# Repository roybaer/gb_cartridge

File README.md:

# GB Cartridge

This repository contains various PCB designs for Game Boy cartridges.

## Board characteristics

The individual designs have the following characteristics:

Board marking     | ROM    | RAM     | RAM backup                 | Technology | Memory Bank Controller
------------------|--------|---------|----------------------------|------------|--------------------------------
ROM+RAM(+BATT)    | 32 KiB | 8 KiB   | external battery/capacitor | SMD        | none
ROM+RAM+BATT      | 32 KiB | 8 KiB   | coin cell battery holder   | SMD        | none
ROM+RAM+BATT EVAL | 32 KiB | 8 KiB   | external battery           | THT        | none
ROM+MBC+RAM+BATT  | 1 MiB  | 128 KiB | coin cell battery holder   | SMD        | 74xx ICs loosely imitating MBC5

So far, only __ROM+RAM+BATT__ and __ROM+RAM+BATT EVAL__ have been manufactured and only the ROM related functionality has been tested.

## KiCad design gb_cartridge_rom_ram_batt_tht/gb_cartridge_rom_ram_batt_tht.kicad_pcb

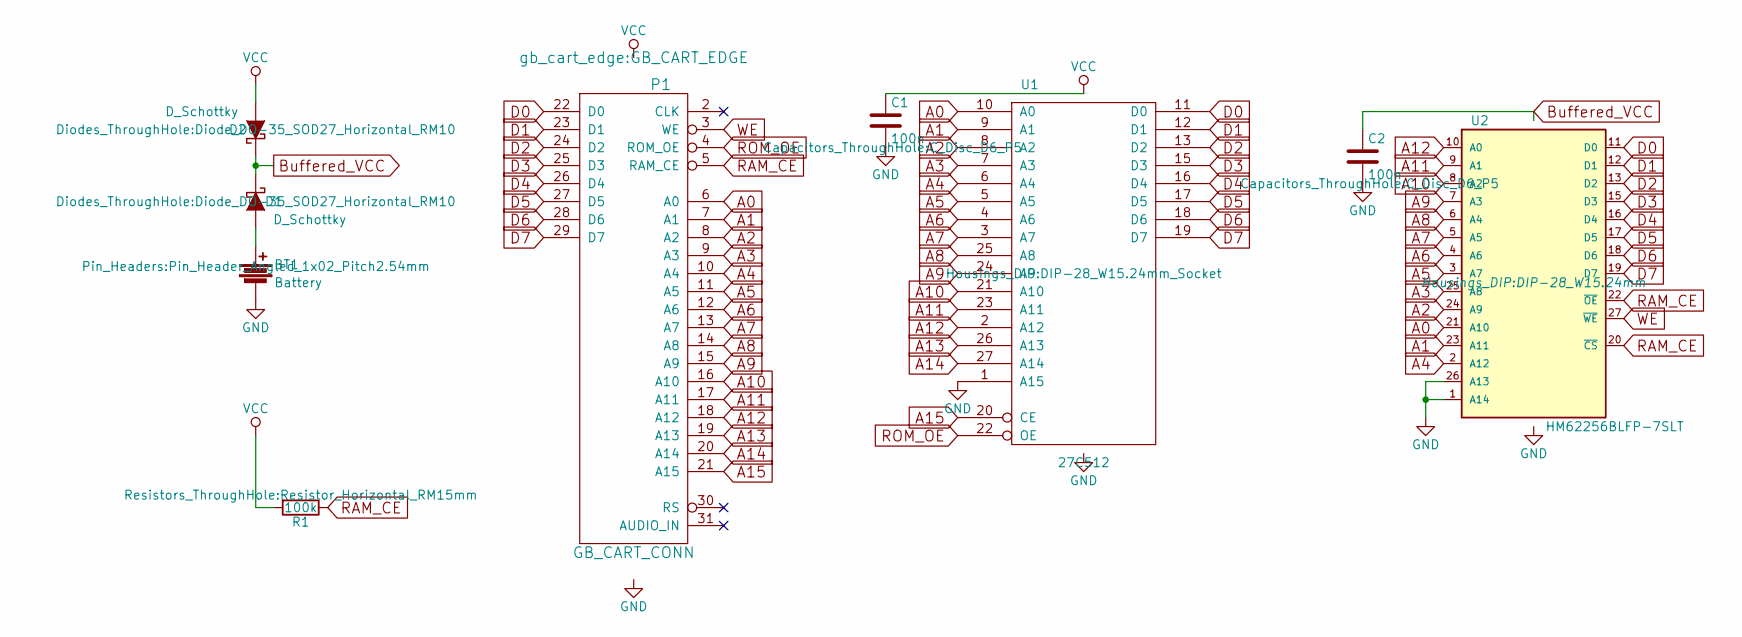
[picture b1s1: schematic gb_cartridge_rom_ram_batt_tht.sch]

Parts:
BT1: Battery; Pin_Header_Angled_1x02_Pitch2.54mm
C1, C2: 100n; C_Disc_D6_P5
D1, D2: D_Schottky; Diode_DO-35_SOD27_Horizontal_RM10
P1: GB_CART_CONN; GB_CART_EDGE
R1: 100k; Resistor_Horizontal_RM15mm
U1: 27C512; DIP-28_W15.24mm_Socket
U2: HM62256BLFP-7SLT; DIP-28_W15.24mm

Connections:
A0: P1.6 (A0), U1.10 (A0), U2.21 (A10)
A1: P1.7 (A1), U1.9 (A1), U2.23 (A11)
A2: P1.8 (A2), U1.8 (A2), U2.24 (A9)
A3: P1.9 (A3), U1.7 (A3), U2.25 (A8)
A4: P1.10 (A4), U1.6 (A4), U2.2 (A12)
A5: P1.11 (A5), U1.5 (A5), U2.3 (A7)
A6: P1.12 (A6), U1.4 (A6), U2.4 (A6)
A7: P1.13 (A7), U1.3 (A7), U2.5 (A5)
A8: P1.14 (A8), U1.25 (A8), U2.6 (A4)
A9: P1.15 (A9), U1.24 (A9), U2.7 (A3)
A10: P1.16 (A10), U1.21 (A10), U2.8 (A2)
A11: P1.17 (A11), U1.23 (A11), U2.9 (A1)
A12: P1.18 (A12), U1.2 (A12), U2.10 (A0)
A13: P1.19 (A13), U1.26 (A13)
A14: P1.20 (A14), U1.27 (A14)
A15: P1.21 (A15), U1.20 (CE)
D0: P1.22 (D0), U1.11 (D0), U2.11 (D0)
D1: P1.23 (D1), U1.12 (D1), U2.12 (D1)
D2: P1.24 (D2), U1.13 (D2), U2.13 (D2)
D3: P1.25 (D3), U1.15 (D3), U2.15 (D3)
D4: P1.26 (D4), U1.16 (D4), U2.16 (D4)
D5: P1.27 (D5), U1.17 (D5), U2.17 (D5)
D6: P1.28 (D6), U1.18 (D6), U2.18 (D6)
D7: P1.29 (D7), U1.19 (D7), U2.19 (D7)
GND: BT1.2, C1.2, C2.2, P1.32 (GND), U1.1 (A15), U1.14 (GND), U2.1 (A14), U2.14 (GND), U2.26 (A13)
unnamed: BT1.1, D1.2 (A)
RAM_CE: P1.5 (RAM_CE), R1.1, U2.20 (~CS), U2.22 (~OE)
ROM_OE: P1.4 (ROM_OE), U1.22 (OE)
WE: P1.3 (WE), U2.27 (~WE)

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
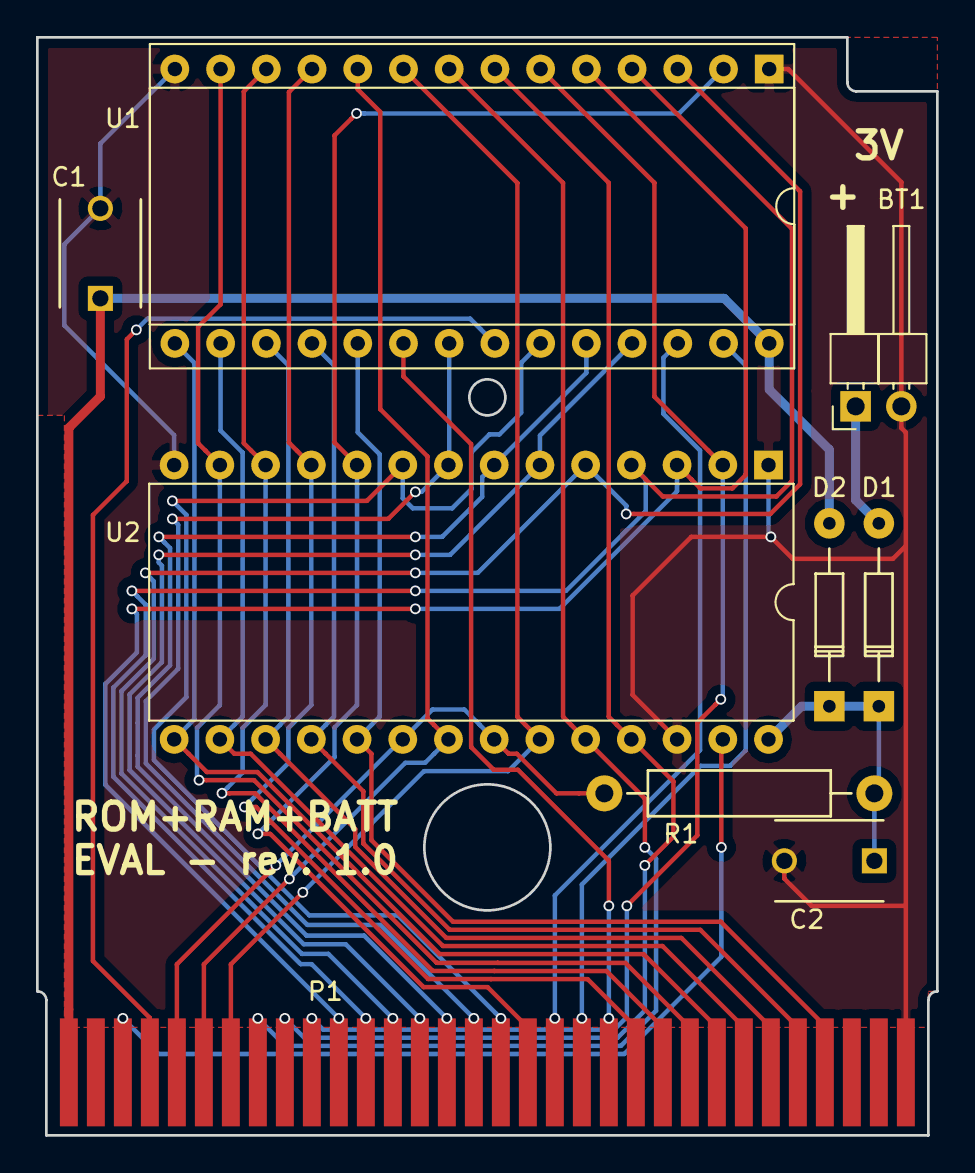
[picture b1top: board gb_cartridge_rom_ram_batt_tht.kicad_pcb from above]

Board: 2 copper layers, 50.0 x 61.0 mm, 9 parts (0 on the bottom side), 30 nets.

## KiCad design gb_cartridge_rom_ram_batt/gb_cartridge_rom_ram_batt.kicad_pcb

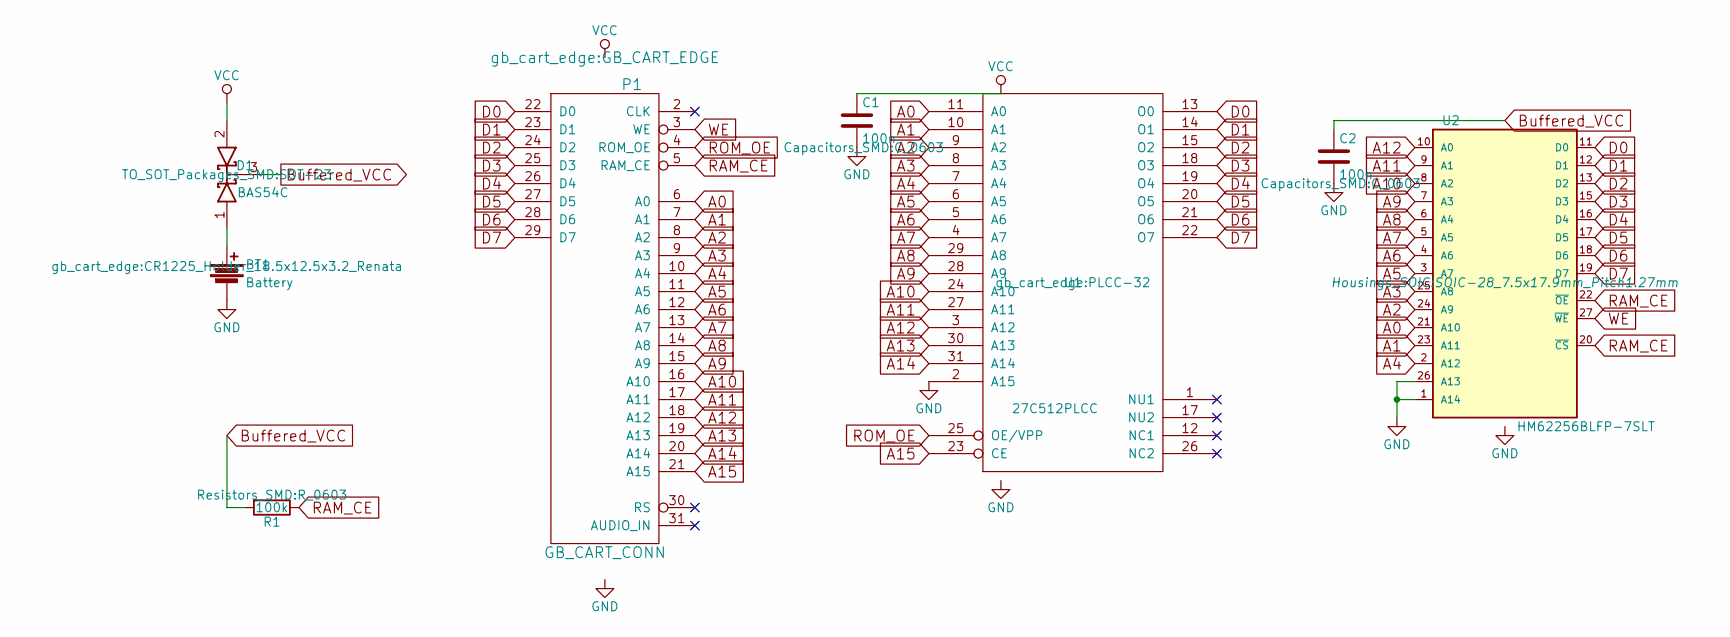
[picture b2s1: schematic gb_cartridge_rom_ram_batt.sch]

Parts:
BT1: Battery; CR1225_Holder_18.5x12.5x3.2_Renata
C1, C2: 100n; C_0603
D1: BAS54C; SOT-23
P1: GB_CART_CONN; GB_CART_EDGE
R1: 100k; R_0603
U1: 27C512PLCC; PLCC-32
U2: HM62256BLFP-7SLT; SOIC-28_7.5x17.9mm_Pitch1.27mm

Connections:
A0: P1.6 (A0), U1.11 (A0), U2.21 (A10)
A1: P1.7 (A1), U1.10 (A1), U2.23 (A11)
A2: P1.8 (A2), U1.9 (A2), U2.24 (A9)
A3: P1.9 (A3), U1.8 (A3), U2.25 (A8)
A4: P1.10 (A4), U1.7 (A4), U2.2 (A12)
A5: P1.11 (A5), U1.6 (A5), U2.3 (A7)
A6: P1.12 (A6), U1.5 (A6), U2.4 (A6)
A7: P1.13 (A7), U1.4 (A7), U2.5 (A5)
A8: P1.14 (A8), U1.29 (A8), U2.6 (A4)
A9: P1.15 (A9), U1.28 (A9), U2.7 (A3)
A10: P1.16 (A10), U1.24 (A10), U2.8 (A2)
A11: P1.17 (A11), U1.27 (A11), U2.9 (A1)
A12: P1.18 (A12), U1.3 (A12), U2.10 (A0)
A13: P1.19 (A13), U1.30 (A13)
A14: P1.20 (A14), U1.31 (A14)
A15: P1.21 (A15), U1.23 (CE)
D0: P1.22 (D0), U1.13 (O0), U2.11 (D0)
D1: P1.23 (D1), U1.14 (O1), U2.12 (D1)
D2: P1.24 (D2), U1.15 (O2), U2.13 (D2)
D3: P1.25 (D3), U1.18 (O3), U2.15 (D3)
D4: P1.26 (D4), U1.19 (O4), U2.16 (D4)
D5: P1.27 (D5), U1.20 (O5), U2.17 (D5)
D6: P1.28 (D6), U1.21 (O6), U2.18 (D6)
D7: P1.29 (D7), U1.22 (O7), U2.19 (D7)
GND: BT1.2, C1.2, C2.2, P1.32 (GND), U1.2 (A15), U1.16 (GND), U2.1 (A14), U2.14 (GND), U2.26 (A13)
unnamed: BT1.1, D1.1 (A)
RAM_CE: P1.5 (RAM_CE), R1.1, U2.20 (~CS), U2.22 (~OE)
ROM_OE: P1.4 (ROM_OE), U1.25 (OE/VPP)
WE: P1.3 (WE), U2.27 (~WE)

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
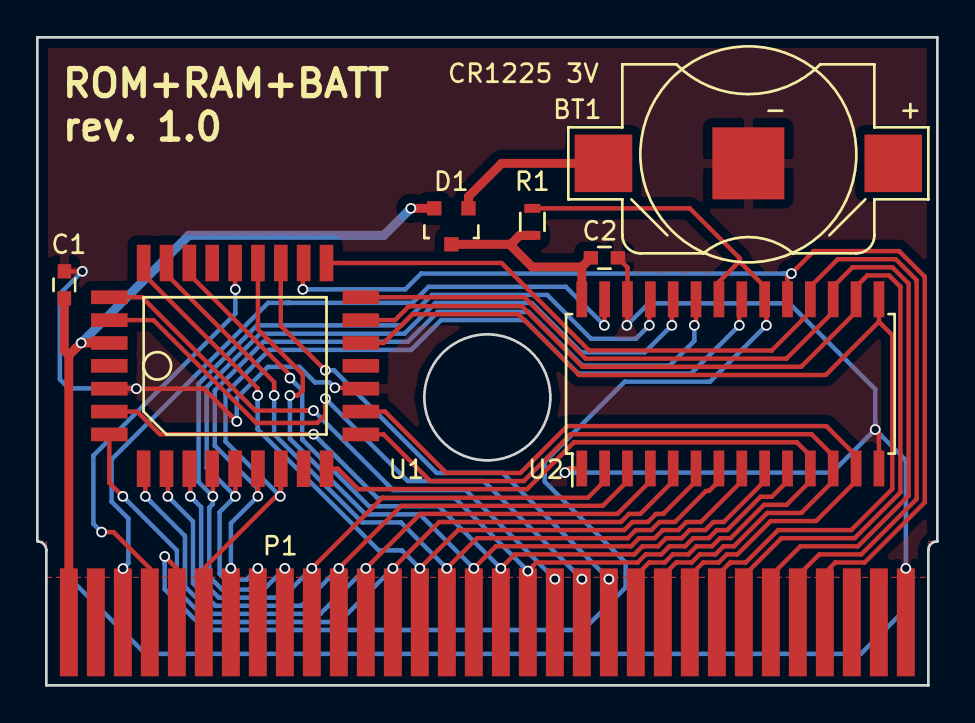
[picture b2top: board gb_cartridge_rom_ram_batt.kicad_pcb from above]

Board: 2 copper layers, 50.0 x 36.0 mm, 8 parts (0 on the bottom side), 30 nets.

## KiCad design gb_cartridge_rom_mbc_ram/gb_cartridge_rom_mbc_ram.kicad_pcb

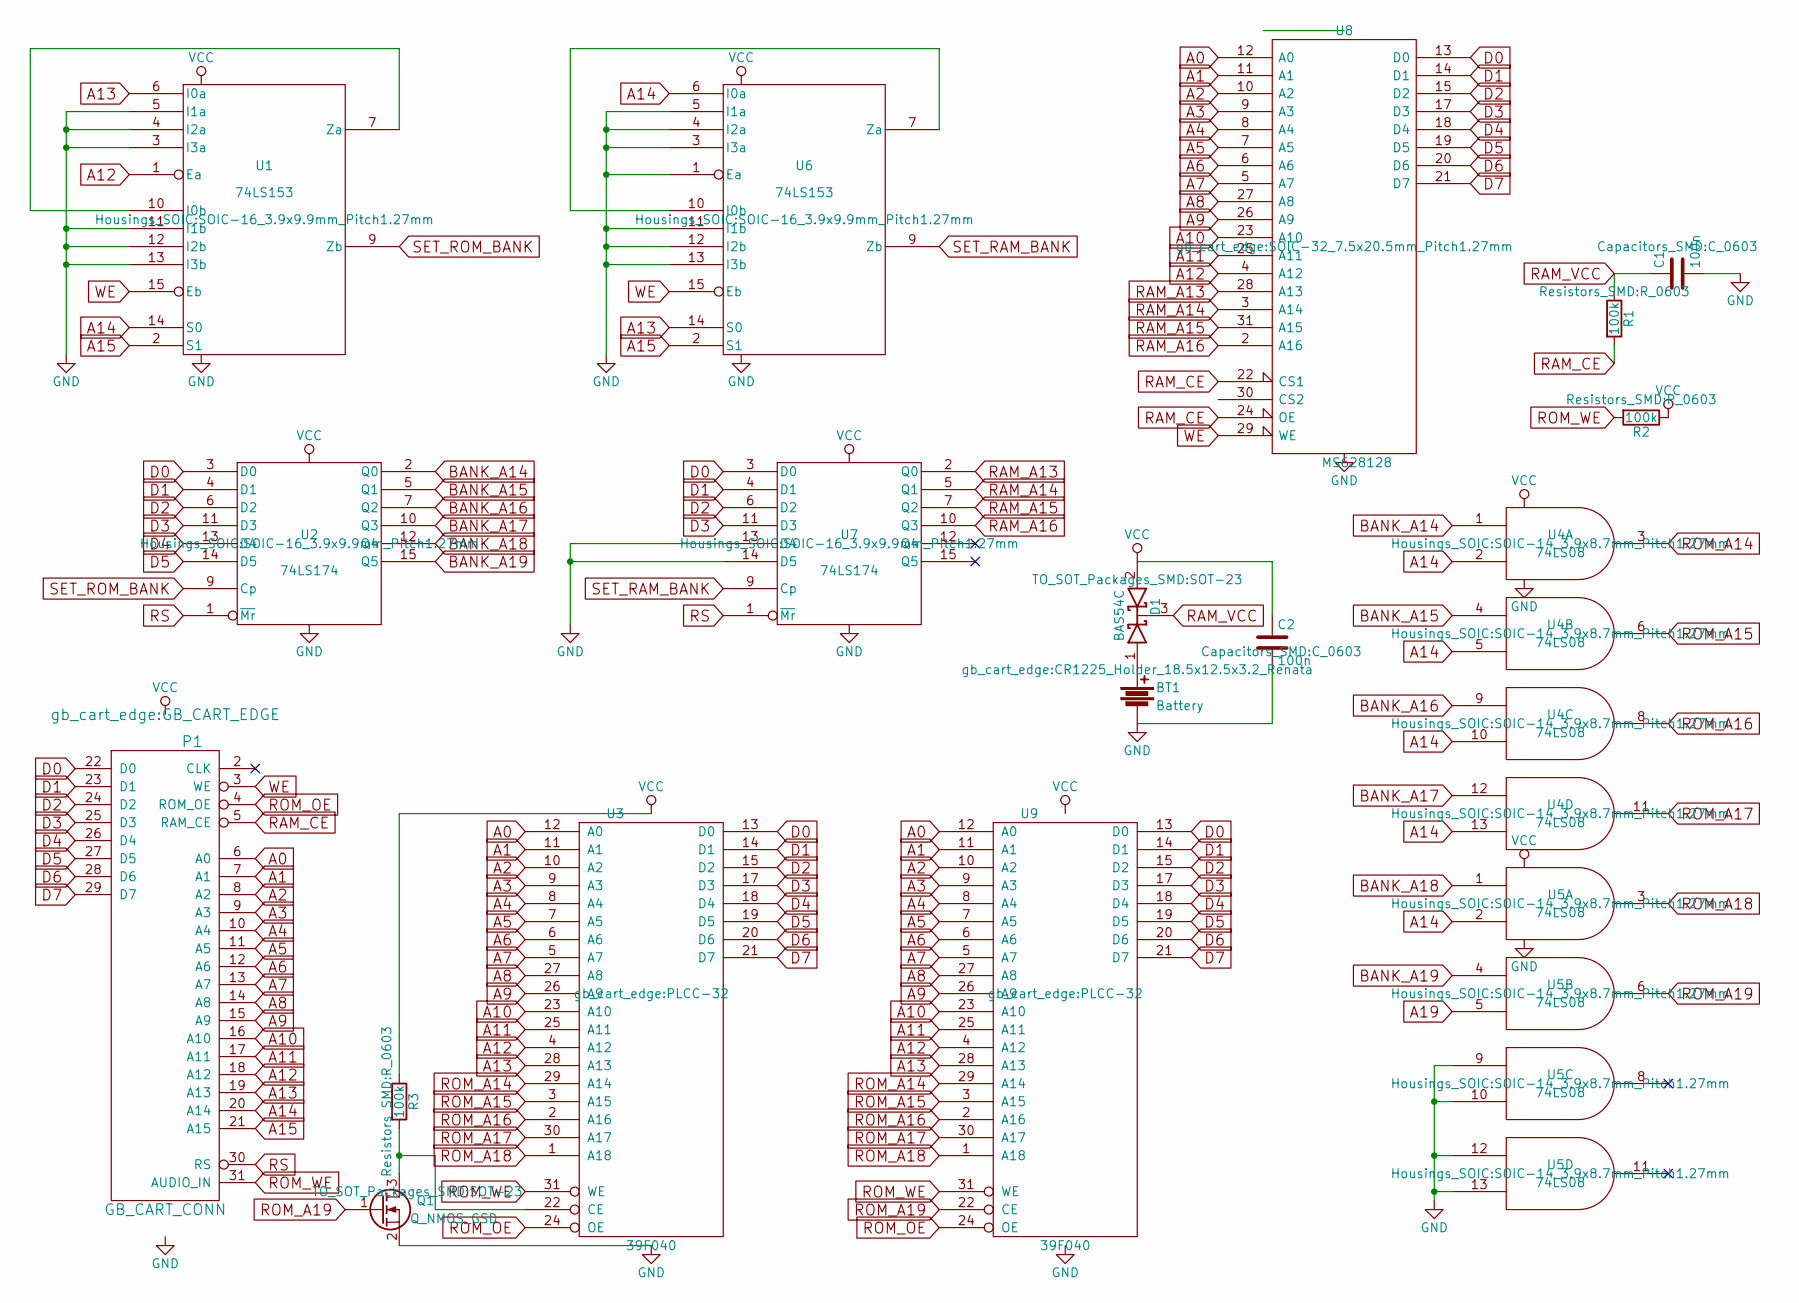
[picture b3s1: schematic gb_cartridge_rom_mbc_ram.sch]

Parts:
BT1: Battery; CR1225_Holder_18.5x12.5x3.2_Renata
C1, C2: 100n; C_0603
D1: BAS54C; SOT-23
P1: GB_CART_CONN; GB_CART_EDGE
Q1: Q_NMOS_GSD; SOT-23
R1, R2, R3: 100k; R_0603
U1, U6: 74LS153; SOIC-16_3.9x9.9mm_Pitch1.27mm
U2, U7: 74LS174; SOIC-16_3.9x9.9mm_Pitch1.27mm
U3, U9: 39F040; PLCC-32
U4, U5: 74LS08; SOIC-14_3.9x8.7mm_Pitch1.27mm
U8: MS628128; SOIC-32_7.5x20.5mm_Pitch1.27mm

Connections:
A0: P1.6 (A0), U3.12 (A0), U8.12 (A0), U9.12 (A0)
A1: P1.7 (A1), U3.11 (A1), U8.11 (A1), U9.11 (A1)
A2: P1.8 (A2), U3.10 (A2), U8.10 (A2), U9.10 (A2)
A3: P1.9 (A3), U3.9 (A3), U8.9 (A3), U9.9 (A3)
A4: P1.10 (A4), U3.8 (A4), U8.8 (A4), U9.8 (A4)
A5: P1.11 (A5), U3.7 (A5), U8.7 (A5), U9.7 (A5)
A6: P1.12 (A6), U3.6 (A6), U8.6 (A6), U9.6 (A6)
A7: P1.13 (A7), U3.5 (A7), U8.5 (A7), U9.5 (A7)
A8: P1.14 (A8), U3.27 (A8), U8.27 (A8), U9.27 (A8)
A9: P1.15 (A9), U3.26 (A9), U8.26 (A9), U9.26 (A9)
A10: P1.16 (A10), U3.23 (A10), U8.23 (A10), U9.23 (A10)
A11: P1.17 (A11), U3.25 (A11), U8.25 (A11), U9.25 (A11)
A12: P1.18 (A12), U1.1 (Ea), U3.4 (A12), U8.4 (A12), U9.4 (A12)
A13: P1.19 (A13), U1.6 (I0a), U3.28 (A13), U6.14 (S0), U9.28 (A13)
A14: P1.20 (A14), U1.14 (S0), U4.2, U4.5, U4.10, U4.13, U5.2, U6.6 (I0a)
A15: P1.21 (A15), U1.2 (S1), U6.2 (S1)
A19: U5.5
BANK_A14: U2.2 (Q0), U4.1
BANK_A15: U2.5 (Q1), U4.4
BANK_A16: U2.7 (Q2), U4.9
BANK_A17: U2.10 (Q3), U4.12
BANK_A18: U2.12 (Q4), U5.1
BANK_A19: U2.15 (Q5), U5.4
D0: P1.22 (D0), U2.3 (D0), U3.13 (D0), U7.3 (D0), U8.13 (D0), U9.13 (D0)
D1: P1.23 (D1), U2.4 (D1), U3.14 (D1), U7.4 (D1), U8.14 (D1), U9.14 (D1)
D2: P1.24 (D2), U2.6 (D2), U3.15 (D2), U7.6 (D2), U8.15 (D2), U9.15 (D2)
D3: P1.25 (D3), U2.11 (D3), U3.17 (D3), U7.11 (D3), U8.17 (D3), U9.17 (D3)
D4: P1.26 (D4), U2.13 (D4), U3.18 (D4), U8.18 (D4), U9.18 (D4)
D5: P1.27 (D5), U2.14 (D5), U3.19 (D5), U8.19 (D5), U9.19 (D5)
D6: P1.28 (D6), U3.20 (D6), U8.20 (D6), U9.20 (D6)
D7: P1.29 (D7), U3.21 (D7), U8.21 (D7), U9.21 (D7)
GND: BT1.2, C1.2, C2.2, P1.32 (GND), Q1.2 (S), U1.3 (I3a), U1.4 (I2a), U1.5 (I1a), U1.8 (GND), U1.11 (I1b), U1.12 (I2b), U1.13 (I3b), U2.8 (GND), U3.16 (GND), U4.7 (GND), U5.7 (GND), U5.9, U5.10, U5.12, U5.13, U6.1 (Ea), U6.3 (I3a), U6.4 (I2a), U6.5 (I1a), U6.8 (GND), U6.11 (I1b), U6.12 (I2b), U6.13 (I3b), U7.8 (GND), U7.13 (D4), U7.14 (D5), U8.16 (GND), U9.16 (GND)
unnamed: BT1.1, D1.1 (A)
unnamed: Q1.3 (D), R3.2, U3.22 (CE)
unnamed: U1.7 (Za), U1.10 (I0b)
unnamed: U6.7 (Za), U6.10 (I0b)
RAM_A13: U7.2 (Q0), U8.28 (A13)
RAM_A14: U7.5 (Q1), U8.3 (A14)
RAM_A15: U7.7 (Q2), U8.31 (A15)
RAM_A16: U7.10 (Q3), U8.2 (A16)
RAM_CE: P1.5 (RAM_CE), R1.2, U8.22 (CS1), U8.24 (OE)
RAM_VCC: C1.1, D1.3 (K), R1.1
ROM_A14: U3.29 (A14), U4.3, U9.29 (A14)
ROM_A15: U3.3 (A15), U4.6, U9.3 (A15)
ROM_A16: U3.2 (A16), U4.8, U9.2 (A16)
ROM_A17: U3.30 (A17), U4.11, U9.30 (A17)
ROM_A18: U3.1 (A18), U5.3, U9.1 (A18)
ROM_A19: Q1.1 (G), U5.6, U9.22 (CE)
ROM_OE: P1.4 (ROM_OE), U3.24 (OE), U9.24 (OE)
ROM_WE: P1.31 (AUDIO_IN), R2.2, U3.31 (WE), U9.31 (WE)
RS: P1.30 (RS), U2.1 (~Mr), U7.1 (~Mr)
SET_RAM_BANK: U6.9 (Zb), U7.9 (Cp)
SET_ROM_BANK: U1.9 (Zb), U2.9 (Cp)
VCC: C2.1, D1.2 (A), P1.1 (VCC), R2.1, R3.1, U1.16 (VCC), U2.16 (VCC), U3.32 (VCC), U4.14 (VCC), U5.14 (VCC), U6.16 (VCC), U7.16 (VCC), U8.32 (VCC), U9.32 (VCC)
WE: P1.3 (WE), U1.15 (Eb), U6.15 (Eb), U8.29 (WE)

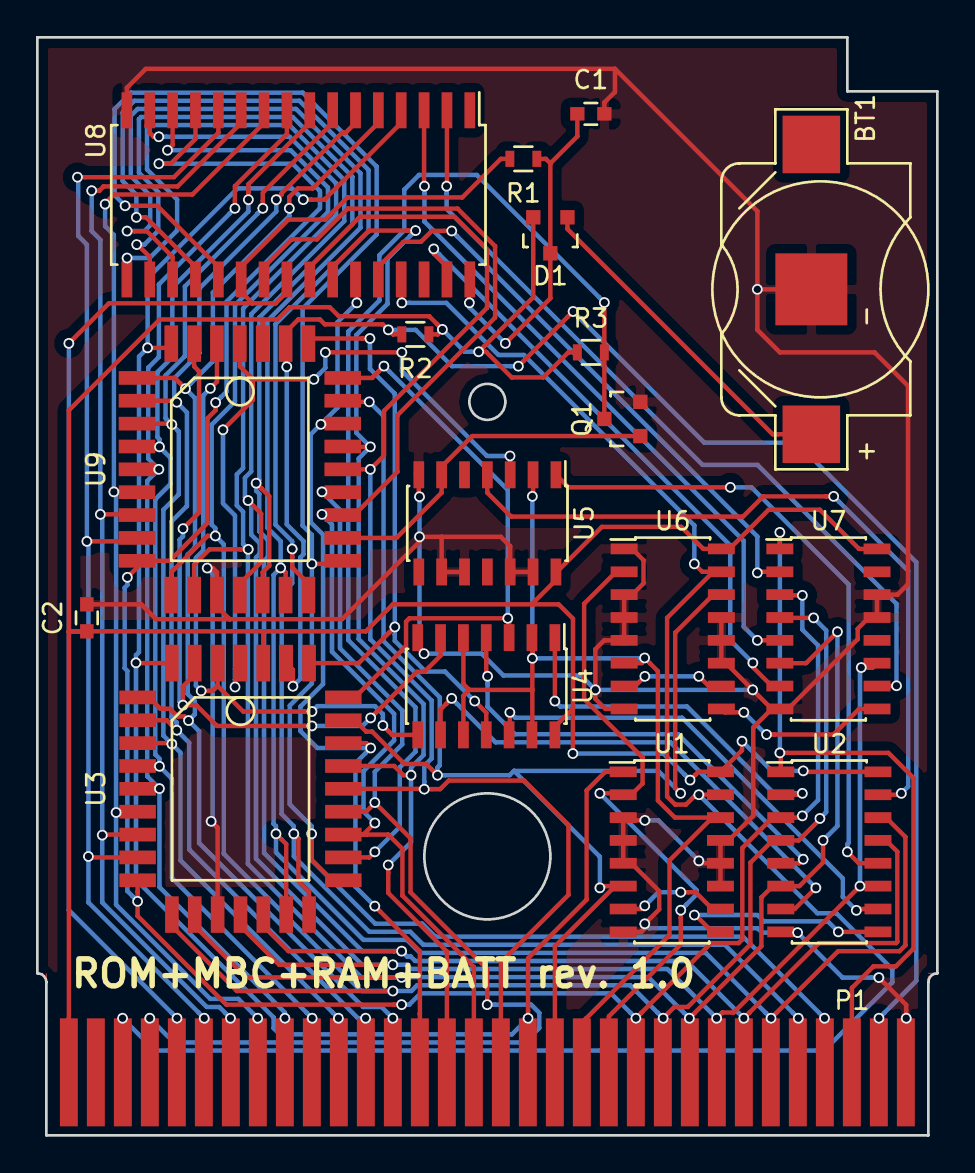
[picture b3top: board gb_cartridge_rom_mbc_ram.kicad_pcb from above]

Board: 2 copper layers, 50.0 x 61.0 mm, 18 parts (0 on the bottom side), 54 nets.

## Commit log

2017-10-30 cartridge with ROM, RAM and wire pads for a backup battery/capacitor
2017-10-30 cartridge with ROM, RAM, bank switching logic and backup battery
2017-10-30 cartridge with ROM, RAM and backup battery (SMD)
2017-10-30 cartridge with ROM, RAM and backup battery connector (THT)
2017-10-30 add README.md
